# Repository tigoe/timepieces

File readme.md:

# Timepieces

This repository was originally the [Clock Club repo](https://github.com/ITPNYU/clock-club), but we moved that to the ITP account. Now this is just a respository of my personal timepiece projects. For the good stuff, see the 
This repository was originally the [Clock Club repo](https://github.com/ITPNYU/clock-club).

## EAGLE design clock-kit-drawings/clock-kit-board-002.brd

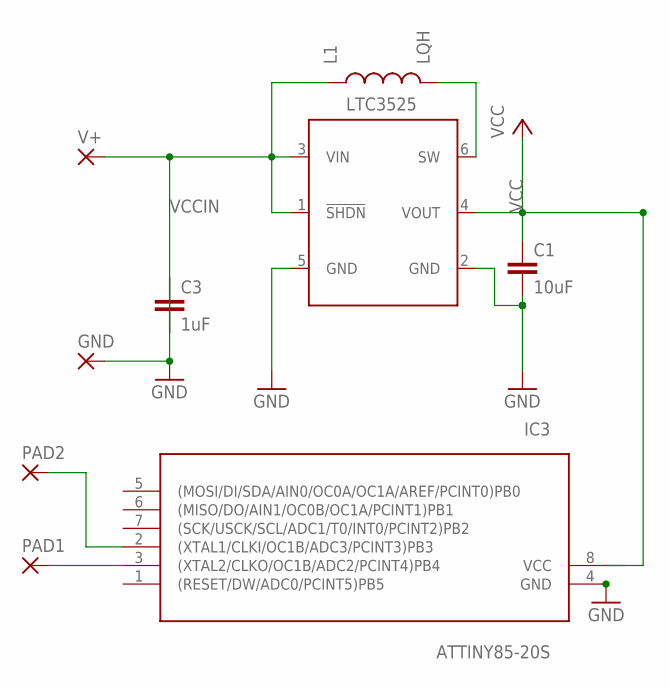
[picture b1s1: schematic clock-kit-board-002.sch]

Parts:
C1: 10uF; 0805
C3: 1uF; 0805
GND: SMD5; SMD2,54-5,08
IC3: ATTINY85-20S; SOIC8
L1: LQH; LQH32
PAD1, PAD2: 1,6/0,9
U1: LTC3525; SC70-6L
V+: SMD5; SMD2,54-5,08

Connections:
GND: C1.2, C3.1, GND.1, IC3.4 (GND), U1.2 (GND), U1.5 (GND)
unnamed: L1.2, U1.6 (SW)
unnamed: IC3.3 ((XTAL2/CLKO/OC1B/ADC2/PCINT4)PB4), PAD1.1
unnamed: IC3.2 ((XTAL1/CLKI/OC1B/ADC3/PCINT3)PB3), PAD2.1
VCC: C1.1, IC3.8 (VCC), U1.4 (VOUT)
VCCIN: C3.2, L1.1, U1.1 (!SHDN), U1.3 (VIN), V+.1

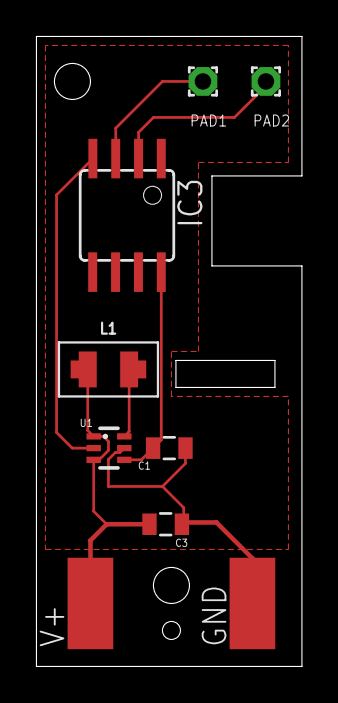
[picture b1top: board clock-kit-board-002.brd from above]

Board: 2 copper layers, 14.8 x 35.0 mm, 9 parts (0 on the bottom side), 6 nets.

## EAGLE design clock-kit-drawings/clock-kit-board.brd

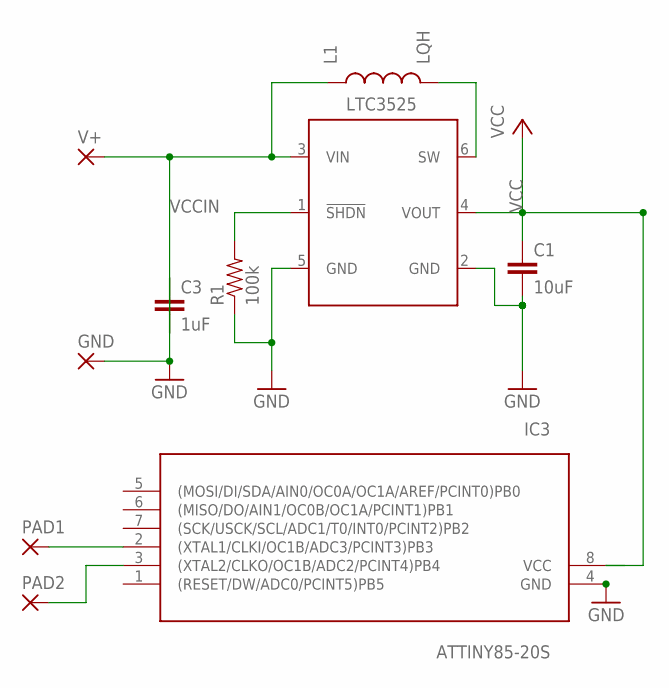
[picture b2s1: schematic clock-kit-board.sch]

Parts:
C1: 10uF; 0805
C3: 1uF; 0805
GND: SMD5; SMD2,54-5,08
IC3: ATTINY85-20S; SOIC8
L1: LQH; LQH32
PAD1, PAD2: 2,54/1,1
R1: 100k; 0805
U1: LTC3525; SC70-6L
V+: SMD5; SMD2,54-5,08

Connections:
GND: C1.2, C3.1, GND.1, IC3.4 (GND), R1.1, U1.2 (GND), U1.5 (GND)
unnamed: L1.2, U1.6 (SW)
unnamed: IC3.2 ((XTAL1/CLKI/OC1B/ADC3/PCINT3)PB3), PAD1.1
unnamed: IC3.3 ((XTAL2/CLKO/OC1B/ADC2/PCINT4)PB4), PAD2.1
SW: R1.2, U1.1 (!SHDN)
VCC: C1.1, IC3.8 (VCC), U1.4 (VOUT)
VCCIN: C3.2, L1.1, U1.3 (VIN), V+.1

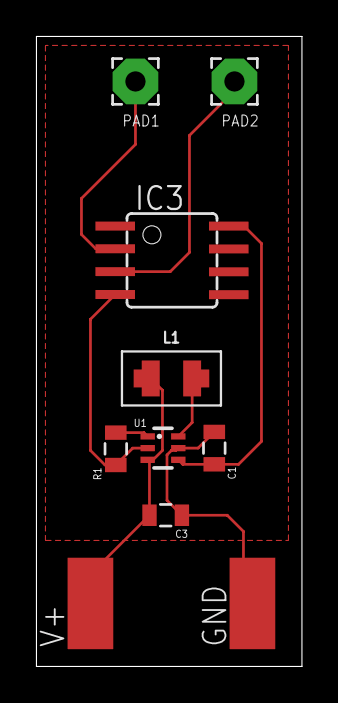
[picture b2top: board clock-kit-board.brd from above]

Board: 2 copper layers, 14.8 x 35.0 mm, 10 parts (0 on the bottom side), 7 nets.

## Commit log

2018-05-06 removed some material that's in clock-club repo now
2018-05-06 Added TomHandClock
2018-05-06 gitignore
2018-08-19 Hourglass updates
2018-08-19 Stuff moved to ITPNYU site
2019-01-07 Updates post clock-club repo
2019-01-07 gitignore cleanup
2020-06-06 update hourglass
2020-06-06 updated clock-kit-drawings
2020-08-12 committed email clock files
2020-08-12 commmitted email clock v2
2024-11-08 added Clock Open Mic show files
2024-11-08 update clock show pieces
2024-11-08 update clock show clocks
